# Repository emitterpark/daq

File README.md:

**DAQ**, Kolaylıkla **IoT (Nesnelerin İnterneti)** projelerinizi
yapabileceğiniz, LoRaWAN kablosuz ağlarıyla uyumlu bir **sensör
aktarıcısıdır**. Üzerindeki **Analog ve Dijital** girişlerine çok
çeşitli sensörleri bağlayabilir, **kilometrelerce** mesafelerden
**kablosuz** yolla bilgi toplayabilirsiniz.

Endüstride mevcut **makineleri** **IoT uyumlu** hale
dönüştürebilirsiniz.

**Akıllı Şehir, Kampüs, Endüstri, Tarım, Otel** ve benzer IoT projenizin
merkezinde **internete** bağlanmış olan bir **LoRaWAN Gateway** cihazı
bulunur. Projenizdeki çok sayıda **DAQ** ünitelerinizden gelen veriler
buradan paketlenerek internete servis edilir. Kendinize ait veya **Açık
kullanım** özelliğindeki diğer kurulu olan LoRaWAN Gateway
cihazlarındanve istasyonlardan faydalanabilirsiniz.

**DAQ** üniteleri, baştan-sona, **The Things Network (TTN)** ve
**myDevices Cayenne** adlı **ücretsiz**

**veri görüntüleme uygulaması** ile tam uyumludur. Uygulamayı indirip
kurduğunuz **PC** ve **Mobil** cihazlarınızda, ünitelerinizden gelen
verileri **zengin görsellerden** takip edebilir, **geçmiş verilere**
erişebilir, **alarm ve uyarıları** bekleyebilirsiniz. Diğer platformlara
kolayca yönlendirebilirsiniz.

LoRaWAN standardı, **ISM** bantlarında, mevcut WiFi, ZigBee, FSK
standartlarına göre daha düşük güçle ve uzak mesafelerde çalışan
kablosuz sensörlerin yapımını mümkün kılar. IP tabanlı olmayıp; **cihaz
kimliği**, uygulama kimliği ve kripto güvenlik anahtarı ile sensörlerin
**IoT platformlarında** takibi için beklenen **esnekliğe ve güvenliğe**
sahiptir.

IoT projeleriniz için **DAQ** ünitelerini, Gateway cihazını ve çeşitli
Analog ve Dijital sensörleri
[[www.example.com]{.ul}](http://www.example.com/) web mağzamızdan satın
alabilirsiniz.

Ürünlerin başlangıç ayarları yapılmış olup **Tak-Çalıştır** özelliği ile
kullanıma hazırdır.

**( Türkiye EU868 MHz )**

**ÖZELLİKLER**

**2 Kanal Analog sensör girişi**

4-20ma endüstriyel otomasyon standardı

Diferansiyel, 16 bit çözünürlük

High ve Low taraf ölçüm yapabilme

Düşük ölçüm direnci, 50 Ohm (Max. 1V gerilim düşümü)

Giriş ölçeklendirme

Sıcaklık, nem, basınç, pozisyon vb. 14 farklı birim tanımlama

Yüksek ve düşük alarm seviyeleri ve kalma süreli histeresis

Aşırı voltaj ve elektrostatik koruma

**2 Kanal Dijital sinyal girişi**

3-24V High seviye

3 farklı dijital birim tanımlama

Dijital alarm ve kalma süreli histeresis

Optoelektronik izolasyon

**5-24V DC endüstriyel besleme girişi**

Dahili 3.3V DC-DC buck dönüştürücü

Alıcı 60mW, Verici 360mW(anlık) güç tüketimi

**Endüstriyel ortama uygun fiziksel tasarım**

Geçmeli tip vidalı klemens girişi

USB micro B konnektör

Aksiyon ledi

Reset butonu

3dbi harici anten

Montaj kulaklı, boyalı alüminyum kutu

24(h)x60(w)x70(l) mm

**Kolay kurulum**

Tak-Çalıştır özelliği, TTN (The Things Network) ve myDevices Cayenne

USB ile PC ve mobil cihazdan parametre ayarlama imkanı

Rapor süresi, alarm seviyeleri, cihaz kimliği, kablosuz çalışma
parametreleri ve diğerleri

**LoRaWAN kablosuz ağ**

LoRaWAN Class A

Lisans gerektirmeyen ISM Bant (EU868, US915, AU915, AS923, IN865, KR920)

20dbm (100mW) radyo verici çıkış gücü

-148dbm radyo alıcı hassasiyeti

Şehir içi 3Km, Şehir dışı 15Km'ye kadar çalışma mesafesi

DevEUI, AppEUI, AppKEY ile OTAA aktivasyonu

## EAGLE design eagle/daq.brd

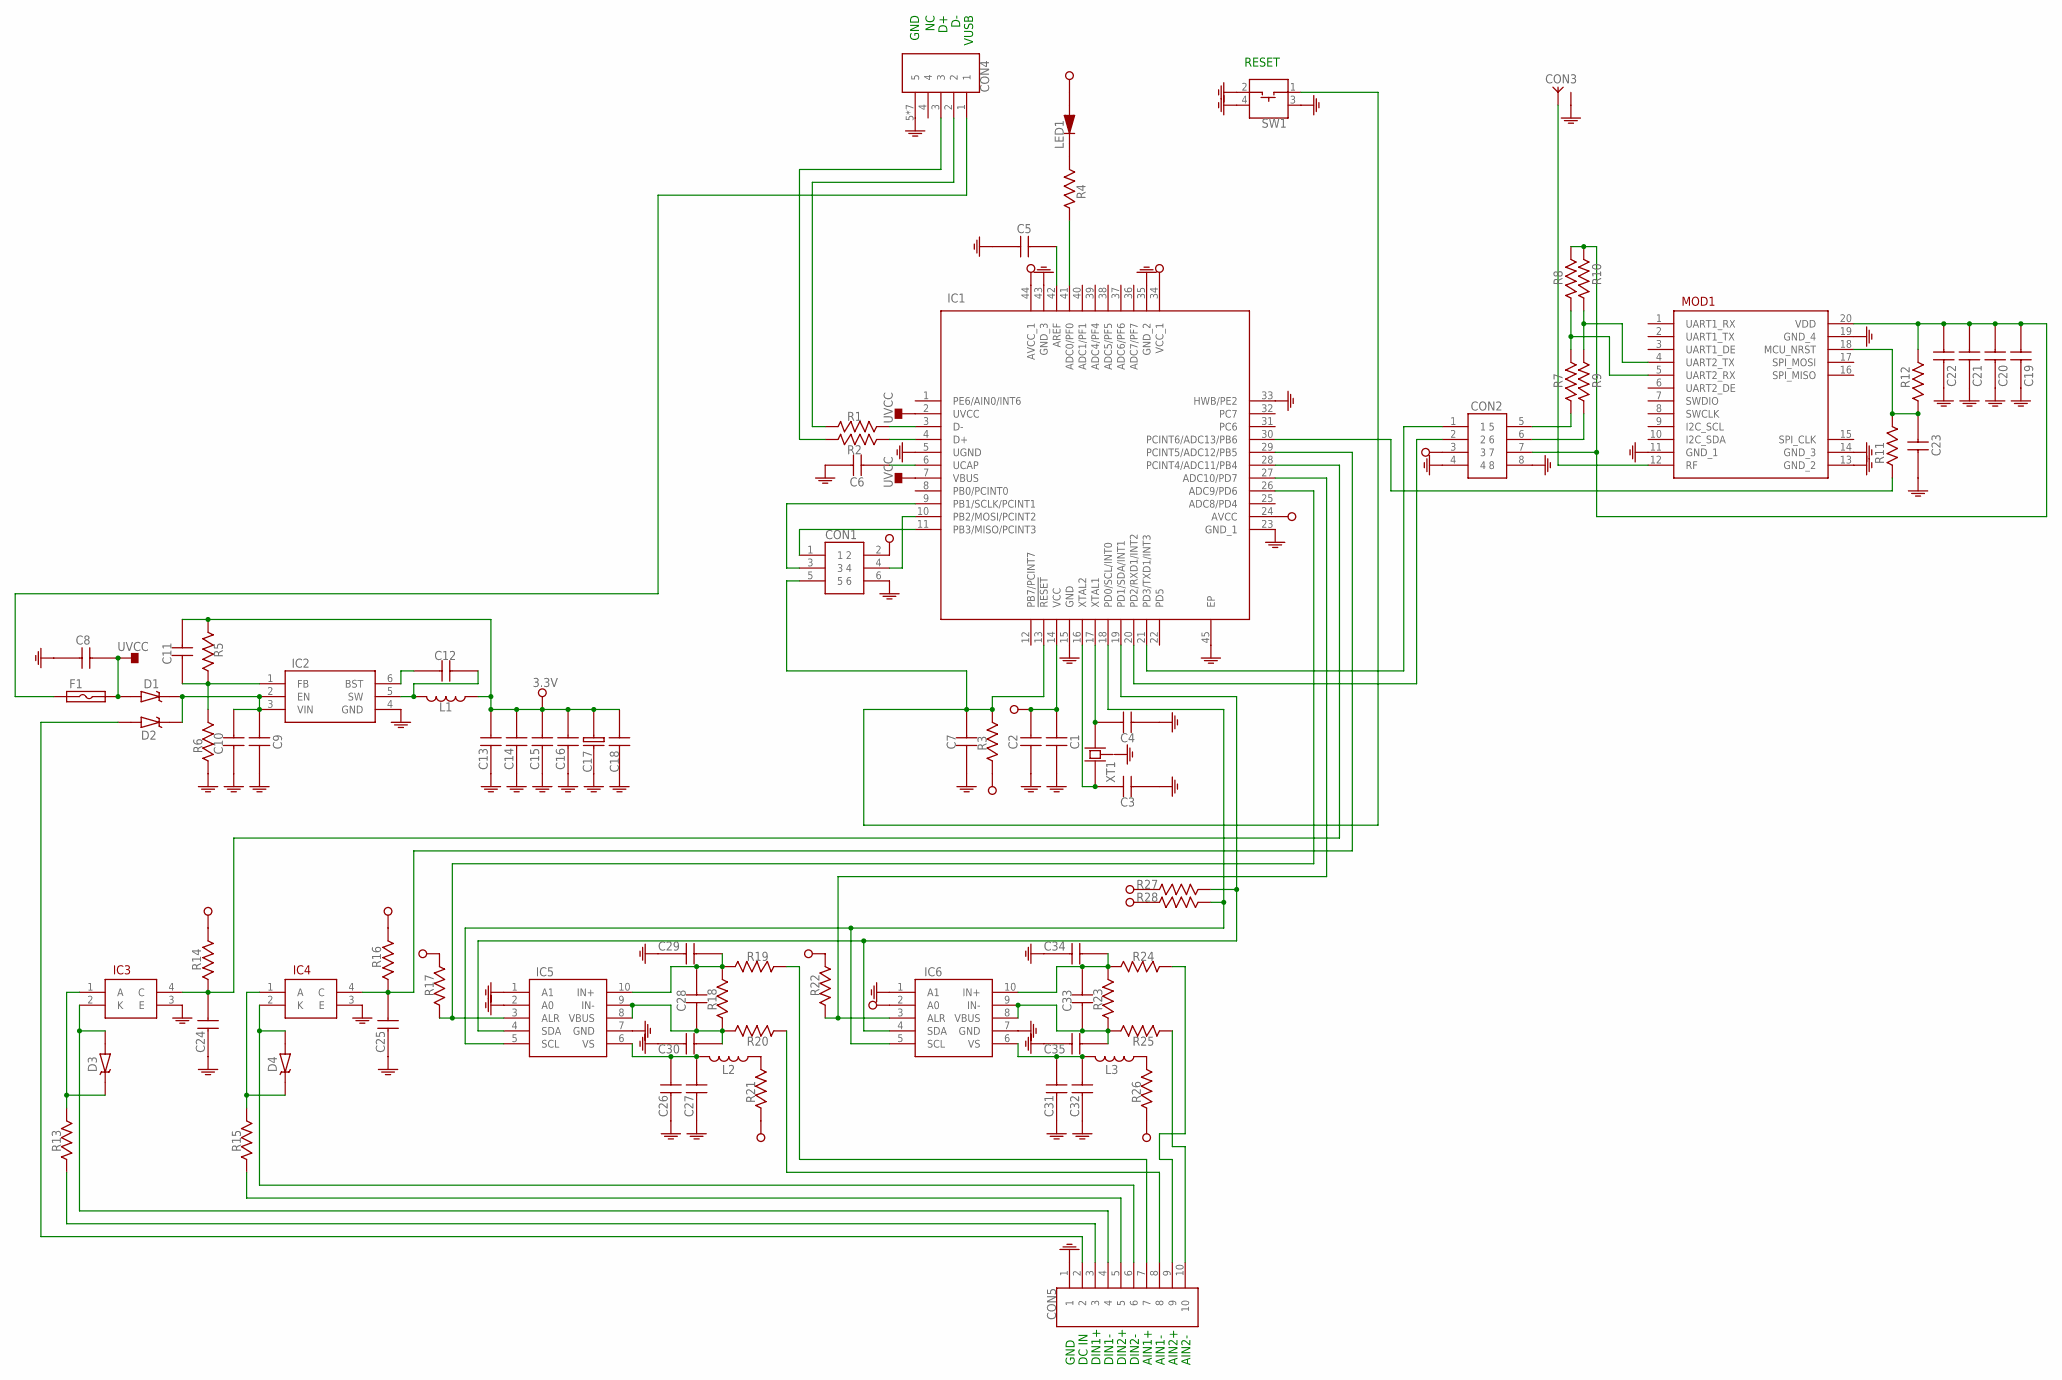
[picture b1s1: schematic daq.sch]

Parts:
C1, C2, C3, C4, C5, C6, C7, C8, C10, C11, C12, C15, C16, C18, C19, C20, C21, C22, C23, C24, C25, C26, C27, C28, C29, C30, C31, C32, C33, C34, C35: CAPACITOR-0603; 0603
C9, C13, C14: CAPACITOR-1206; 1206
C17: CAPACITOR-SMD-8
CON1: ISP
CON2: HEADER-8P-2R-DIP-2_54MM
CON3: SMA-RF
CON4: USB-MICRO-B-SMD
CON5: 15EDGRC-3.81-10P
D1, D2, D3, D4: DIODE-SCHOTTKY; SOD123-DIODE
F1: FUSE-1206; 1206
IC1: ATMEGA32U4-MU; QFN-44
IC2: AP63200; SOT23-6
IC3, IC4: OPTO-SMD
IC5, IC6: INA226; VSSOP-10
L1: INDUCTOR-CDRH127R
L2, L3: INDUCTOR-0805; 0805
LED1: LED-3MM-RA
MOD1: RAK4200
R1, R2, R3, R4, R5, R6, R7, R8, R9, R10, R11, R12, R14, R16, R17, R21, R22, R26, R27, R28: RESISTOR-0603; 0603
R13, R15, R18, R19, R20, R23, R24, R25: RESISTOR-0805; 0805
SW1: B3F-3150-52-55
XT1: CRYSTAL-5032-4P

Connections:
GND: C1.1, C2.1, C3.1, C4.1, C5.1, C6.1, C7.1, C8.1, C9.1, C10.1, C13.1, C14.1, C15.1, C16.1, C17.1, C18.1, C19.1, C20.1, C21.1, C22.1, C23.1, C24.1, C25.1, C26.1, C27.1, C29.2, C30.2, C31.1, C32.1, C34.2, C35.2, CON1.6, CON2.4, CON2.8, CON3.2 (GND), CON3.3 (GND), CON3.4 (GND), CON3.5 (GND), CON4.5, CON4.6 (5), CON4.7 (5), CON4.8 (5), CON4.9 (5), CON4.10 (5), CON4.11 (5), CON5.1, IC1.5 (UGND), IC1.15 (GND), IC1.23 (GND_1), IC1.33 (HWB/PE2), IC1.35 (GND_2), IC1.43 (GND_3), IC1.45 (EP), IC2.4 (GND), IC3.3 (E), IC4.3 (E), IC5.1 (A1), IC5.2 (A0), IC5.7 (GND), IC6.1 (A1), IC6.7 (GND), MOD1.11 (GND_1), MOD1.13 (GND_2), MOD1.14 (GND_3), MOD1.19 (GND_4), R6.1, SW1.2, SW1.3, SW1.4, XT1.2 (GND), XT1.4 (GND)
unnamed: IC1.41 (ADC0/PF0), R4.1
unnamed: C23.2, MOD1.18 (MCU_NRST), R11.1, R12.1
unnamed: CON1.1, IC1.11 (PB3/MISO/PCINT3)
unnamed: CON3.1 (ANT), MOD1.12 (RF)
unnamed: C28.1, C30.1, IC5.8 (VBUS), IC5.9 (IN-), R18.1, R20.2
unnamed: MOD1.5 (UART2_RX), R7.2, R8.1
unnamed: CON5.2, D2.2 (A)
unnamed: C33.1, C35.1, IC6.8 (VBUS), IC6.9 (IN-), R23.1, R25.2
unnamed: CON1.4, IC1.10 (PB2/MOSI/PCINT2)
unnamed: C3.2, IC1.16 (XTAL2), XT1.1
unnamed: C28.2, C29.1, IC5.10 (IN+), R18.2, R19.2
unnamed: C4.2, IC1.17 (XTAL1), XT1.3 (2)
unnamed: C19.2, C20.2, C21.2, C22.2, CON2.7, MOD1.20 (VDD), R8.2, R10.2, R12.2
unnamed: CON2.5, R7.1
unnamed: IC1.27 (ADC10/PD7), IC6.3 (ALR), R22.2
unnamed: CON2.6, R9.1
unnamed: CON4.2, R1.1
unnamed: CON4.3, R2.1
unnamed: D3.1 (K), IC3.1 (A), R13.2
unnamed: IC1.30 (PCINT6/ADC13/PB6), R11.2
unnamed: IC1.26 (ADC9/PD6), IC5.3 (ALR), R17.2
unnamed: CON2.1, IC1.21 (PD3/TXD1/INT3)
unnamed: CON2.2, IC1.20 (PD2/RXD1/INT2)
unnamed: LED1.K, R4.2
unnamed: L3.1, R26.2
unnamed: CON5.8, R20.1
unnamed: CON5.7, R19.1
unnamed: CON5.10, R25.1
unnamed: C5.2, IC1.42 (AREF)
unnamed: C25.2, IC1.29 (PCINT5/ADC12/PB5), IC4.4 (C), R16.2
unnamed: D4.1 (K), IC4.1 (A), R15.2
unnamed: C6.2, IC1.6 (UCAP)
unnamed: C24.2, IC1.28 (PCINT4/ADC11/PB4), IC3.4 (C), R14.2
unnamed: CON5.9, R24.1
unnamed: MOD1.4 (UART2_TX), R9.2, R10.1
unnamed: C33.2, C34.1, IC6.10 (IN+), R23.2, R24.2
unnamed: C7.2, CON1.5, IC1.13 (!RESET), R3.2, SW1.1
unnamed: C31.2, C32.2, IC6.6 (VS), L3.2
unnamed: IC1.3 (D-), R1.2
unnamed: IC1.4 (D+), R2.2
unnamed: CON1.3, IC1.9 (PB1/SCLK/PCINT1)
unnamed: CON5.6, D4.2 (A), IC4.2 (K)
unnamed: CON5.4, D3.2 (A), IC3.2 (K)
unnamed: CON5.5, R15.1
unnamed: CON4.1, F1.1
unnamed: C9.2, C10.2, D1.1 (K), D2.1 (K), IC2.2 (EN), IC2.3 (VIN)
unnamed: C12.2, IC2.6 (BST)
unnamed: C12.1, IC2.5 (SW), L1.2
unnamed: L2.1, R21.2
unnamed: C11.1, IC2.1 (FB), R5.2, R6.2
unnamed: IC1.18 (PD0/SCL/INT0), IC5.5 (SCL), IC6.5 (SCL), R28.2
unnamed: C26.2, C27.2, IC5.6 (VS), L2.2
unnamed: IC1.19 (PD1/SDA/INT1), IC5.4 (SDA), IC6.4 (SDA), R27.2
unnamed: CON5.3, R13.1
UVCC: C8.2, D1.2 (A), F1.2, IC1.2 (UVCC), IC1.7 (VBUS)
VCC: C1.2, C2.2, C11.2, C13.2, C14.2, C15.2, C16.2, C17.2, C18.2, CON1.2, CON2.3, IC1.14 (VCC), IC1.24 (AVCC), IC1.34 (VCC_1), IC1.44 (AVCC_1), IC6.2 (A0), L1.1, LED1.A, R3.1, R5.1, R14.1, R16.1, R17.1, R21.1, R22.1, R26.1, R27.1, R28.1

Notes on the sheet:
DC IN
GND
AIN1+
AIN1-
AIN2+
AIN2-
DIN1+
DIN1-
DIN2+
DIN2-
VUSB
RESET

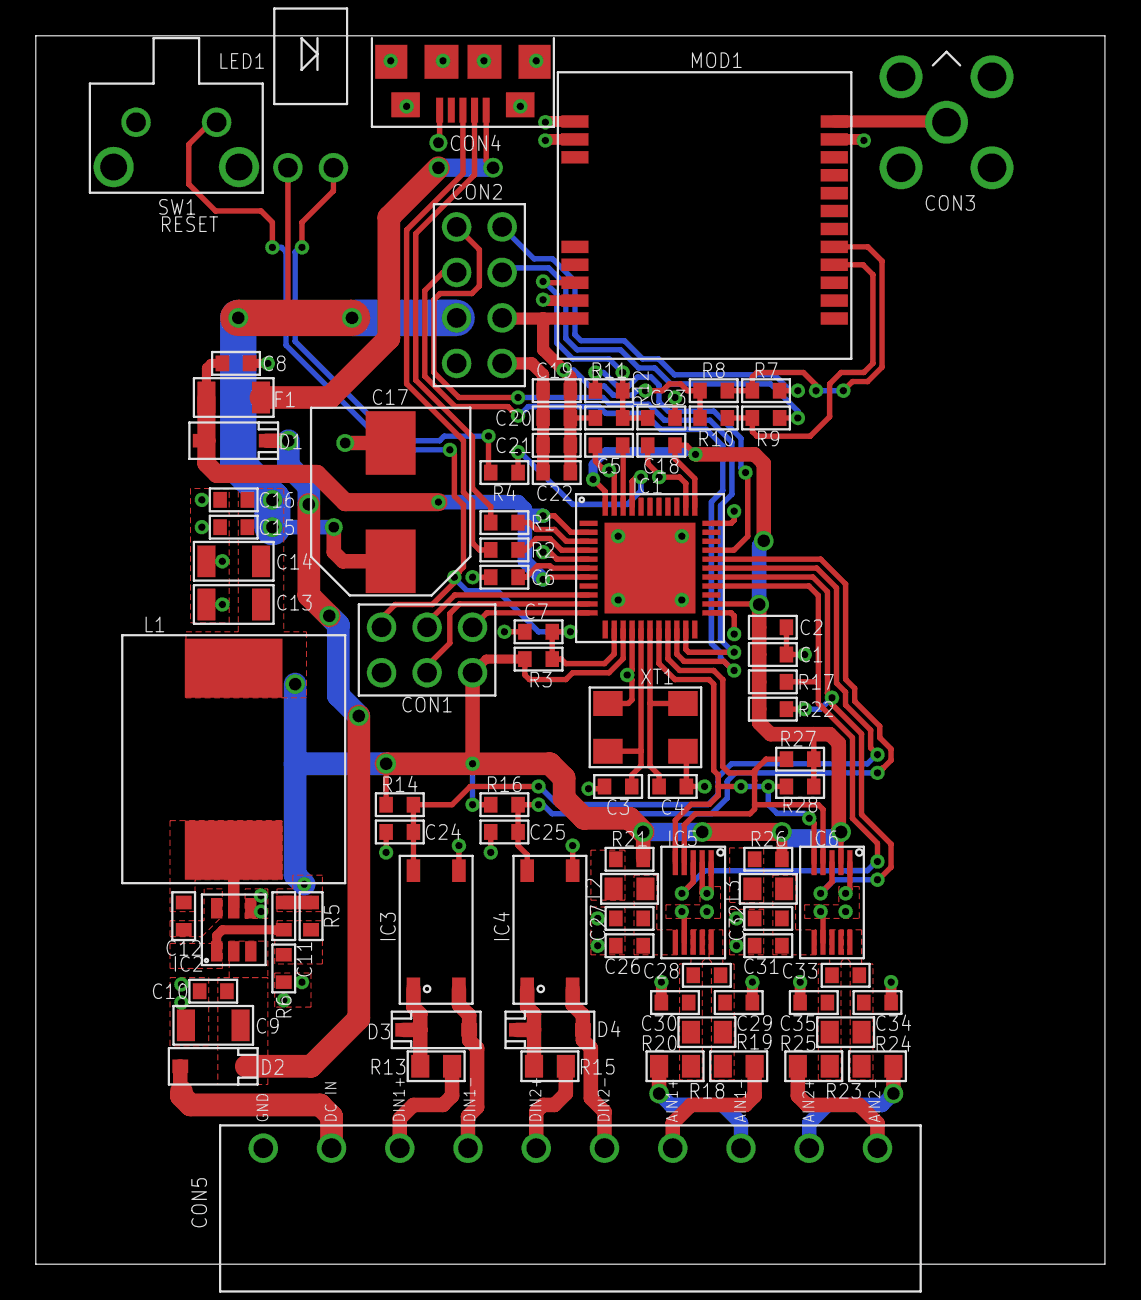
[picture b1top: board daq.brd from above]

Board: 2 copper layers, 59.7 x 68.6 mm, 86 parts (0 on the bottom side), 57 nets.

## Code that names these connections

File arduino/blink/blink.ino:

const uint8_t AN_ALR_PIN[2]       = {12, 6};          // PD6/ADC9, PD7/ADC10
const uint8_t DIG_PIN[2]          = {8, 9};           // PB4/ADC11/PCINT4, PB5/ADC12/PCINT5
const uint8_t LORA_RES_PIN        = 10;               // PB6/ADC13/PCINT6
const uint8_t RANDOM_PIN          = A0;               // PF7/ADC7 
const uint8_t LED_PIN             = A5;               // PF0/ADC0

void setup() {    
  setPin();   
}
void loop() {   
  digitalWrite(LED_PIN, LOW);
  delay(200);
  digitalWrite(LED_PIN, HIGH);
  delay(200); 
}
void setPin() {
  for (uint8_t ch = 0; ch < 2; ch++) {
    pinMode(AN_ALR_PIN[ch], INPUT);
    pinMode(DIG_PIN[ch], INPUT);
  }
  pinMode(LORA_RES_PIN, OUTPUT);
  pinMode(LED_PIN, OUTPUT);
  digitalWrite(LORA_RES_PIN, LOW);
  digitalWrite(LED_PIN, HIGH);  
}

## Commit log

2020-07-24 init
